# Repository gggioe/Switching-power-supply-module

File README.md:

# Switching-power-supply-module
SIC450 power supply board

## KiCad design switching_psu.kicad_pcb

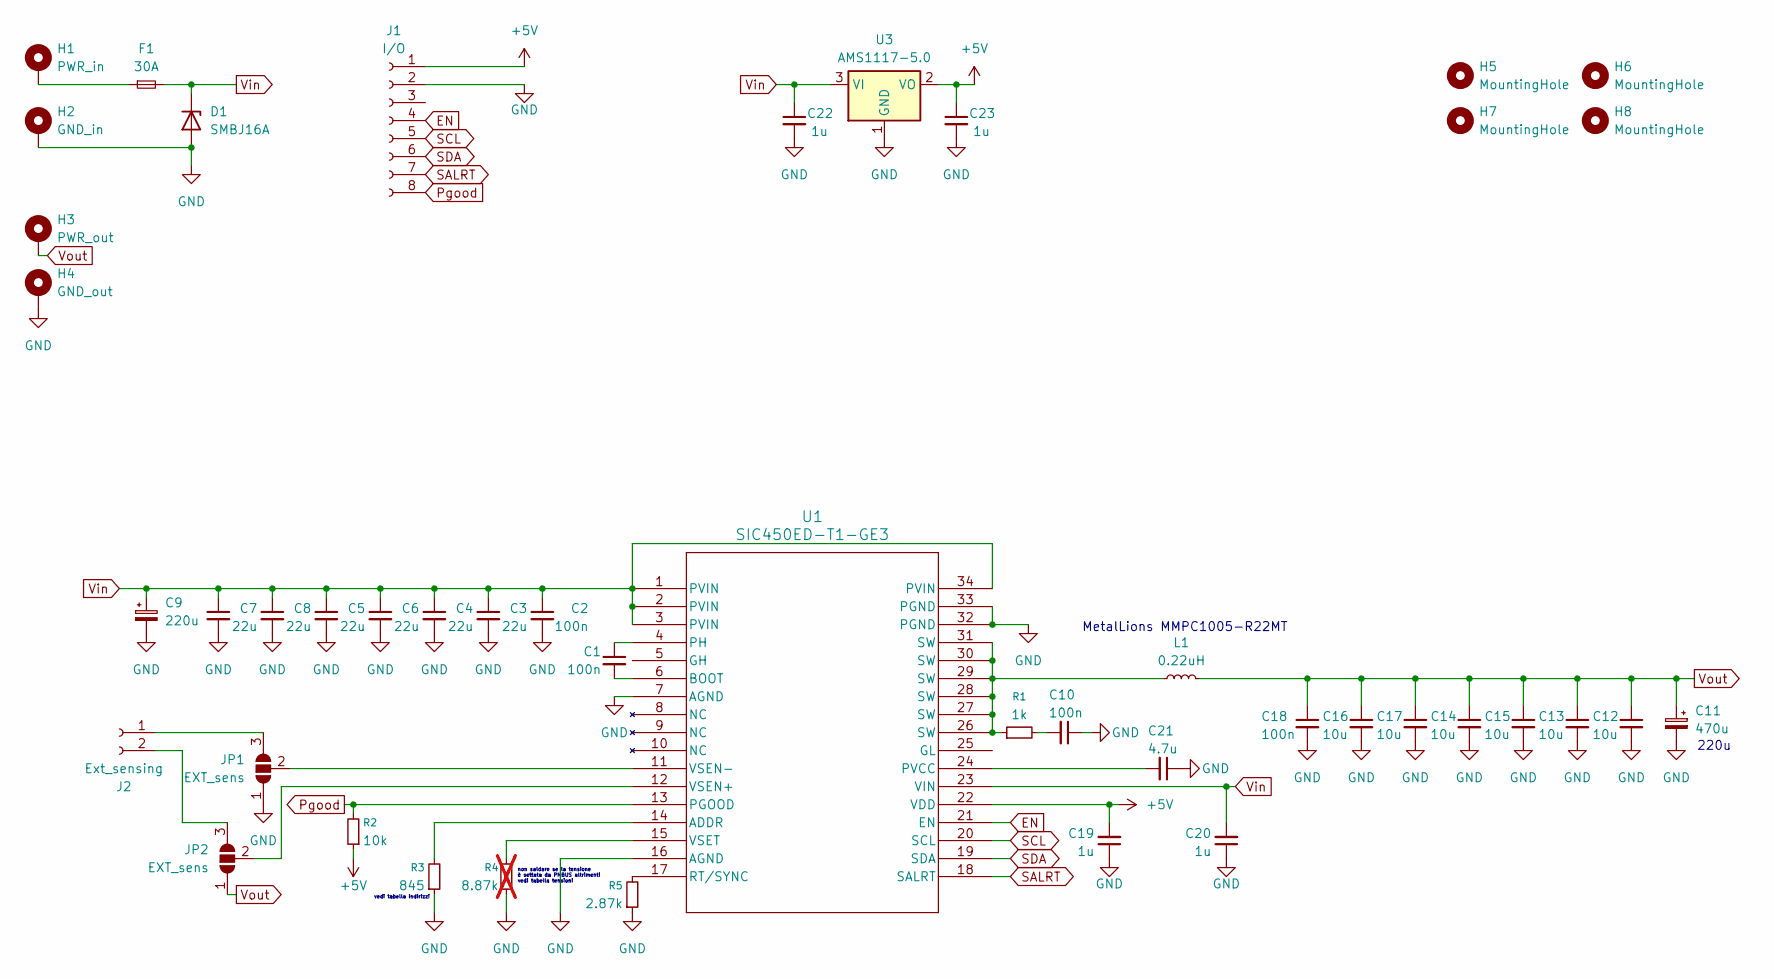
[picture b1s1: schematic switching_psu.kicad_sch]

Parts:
C1, C2, C10, C18: 100n; C_0603_1608Metric_Pad1.08x0.95mm_HandSolder
C3, C4, C5, C6, C7, C8: 22u; C_0805_2012Metric_Pad1.18x1.45mm_HandSolder
C9: 220u; C_Elec_6.3x7.7
C11: 470u; C_Elec_6.3x7.7
C12, C13, C14, C15, C16, C17: 10u; C_0603_1608Metric_Pad1.08x0.95mm_HandSolder
C19, C20, C22, C23: 1u; C_0603_1608Metric_Pad1.08x0.95mm_HandSolder
C21: 4.7u; C_0603_1608Metric_Pad1.08x0.95mm_HandSolder
D1: SMBJ16A; D_SMB_Handsoldering
F1: 30A; Fuse_1206_3216Metric_Pad1.42x1.75mm_HandSolder
H1: PWR_in; MountingHole_4.3mm_M4_Pad_Via
H2: GND_in; MountingHole_4.3mm_M4_Pad_Via
H3: PWR_out; MountingHole_4.3mm_M4_Pad_Via
H4: GND_out; MountingHole_4.3mm_M4_Pad_Via
H5, H6, H7, H8: MountingHole; MountingHole_4.3mm_M4
J1: I/O; JST_PH_B8B-PH-K_1x08_P2.00mm_Vertical
J2: Ext_sensing; JST_PH_B2B-PH-K_1x02_P2.00mm_Vertical
JP1, JP2: EXT_sens; SolderJumper-3_P1.3mm_Open_RoundedPad1.0x1.5mm
L1: 0.22uH; L_12x12mm_H6mm
R1: 1k; R_0603_1608Metric_Pad0.98x0.95mm_HandSolder
R2: 10k; R_0603_1608Metric_Pad0.98x0.95mm_HandSolder
R3: 845; R_0603_1608Metric_Pad0.98x0.95mm_HandSolder
R4: 8.87k; R_0603_1608Metric_Pad0.98x0.95mm_HandSolder; not fitted
R5: 2.87k; R_0603_1608Metric_Pad0.98x0.95mm_HandSolder
U1: SIC450ED-T1-GE3; POWERPAK_MLP34-57_VIS
U3: AMS1117-5.0; SOT-223-3_TabPin2

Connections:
+5V: C19.2, C23.1, J1.1, R2.1, U1.22 (VDD), U3.2 (VO)
EN: J1.4, U1.21 (EN)
GND: C2.2, C3.2, C4.2, C5.2, C6.2, C7.2, C8.2, C9.2, C10.1, C11.2, C12.2, C13.2, C14.2, C15.2, C16.2, C17.2, C18.2, C19.1, C20.1, C21.1, C22.2, C23.2, D1.2 (A), H2.1, H4.1, J1.2, JP1.1 (A), R3.1, R4.1, R5.1, U1.7 (AGND), U1.16 (AGND), U1.32 (PGND), U1.33 (PGND), U3.1 (GND)
unnamed: C10.2, R1.2
unnamed: F1.1, H1.1
unnamed: J2.1, JP1.3 (B)
unnamed: J2.2, JP2.3 (B)
unnamed: JP1.2 (C), U1.11 (VSEN-)
unnamed: JP2.2 (C), U1.12 (VSEN+)
unnamed: L1.1, R1.1, U1.26 (SW), U1.27 (SW), U1.28 (SW), U1.29 (SW), U1.30 (SW), U1.31 (SW)
unnamed: R3.2, U1.14 (ADDR)
unnamed: C1.2, U1.6 (BOOT)
unnamed: C1.1, U1.4 (PH)
unnamed: C21.2, U1.24 (PVCC)
unnamed: R5.2, U1.17 (RT/SYNC)
unnamed: R4.2, U1.15 (VSET)
Pgood: J1.8, R2.2, U1.13 (PGOOD)
SALRT: J1.7, U1.18 (SALRT)
SCL: J1.5, U1.20 (SCL)
SDA: J1.6, U1.19 (SDA)
Vin: C2.1, C3.1, C4.1, C5.1, C6.1, C7.1, C8.1, C9.1, C20.2, C22.1, D1.1 (K), F1.2, U1.1 (PVIN), U1.2 (PVIN), U1.3 (PVIN), U1.23 (VIN), U1.34 (PVIN), U3.3 (VI)
Vout: C11.1, C12.1, C13.1, C14.1, C15.1, C16.1, C17.1, C18.1, H3.1, JP2.1 (A), L1.2

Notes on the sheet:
non saldare se la tensione è settata da PMBUS altrimenti vedi tabella tensioni
vedi tabella indirizzi
220u
MetalLions MMPC1005-R22MT

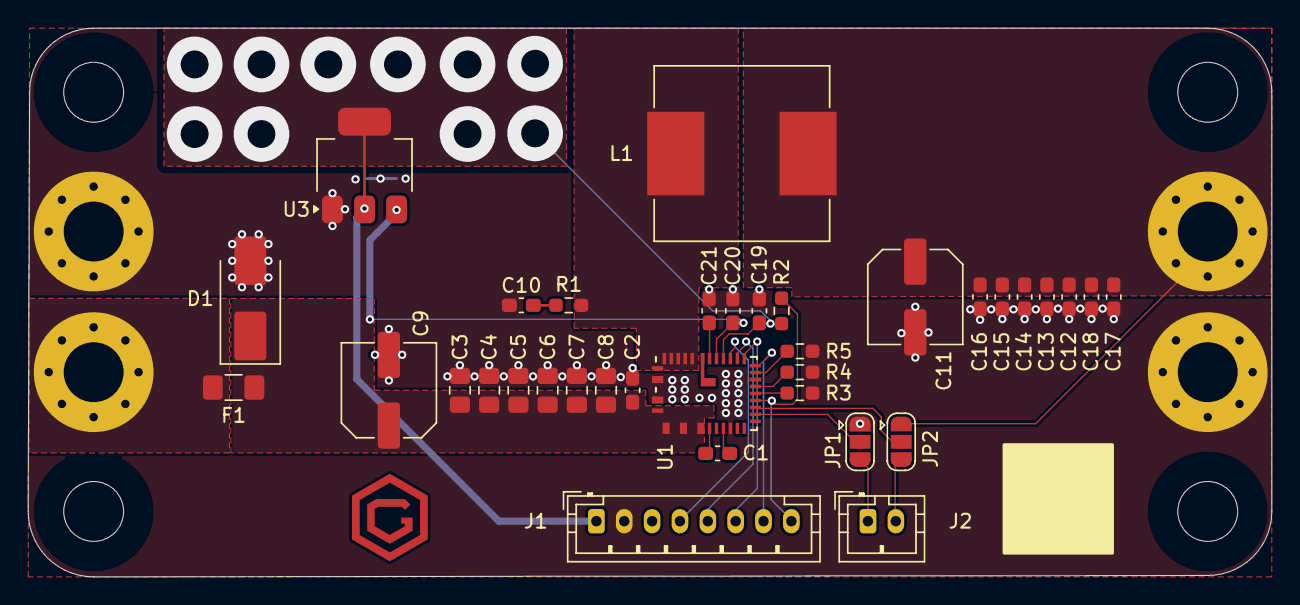
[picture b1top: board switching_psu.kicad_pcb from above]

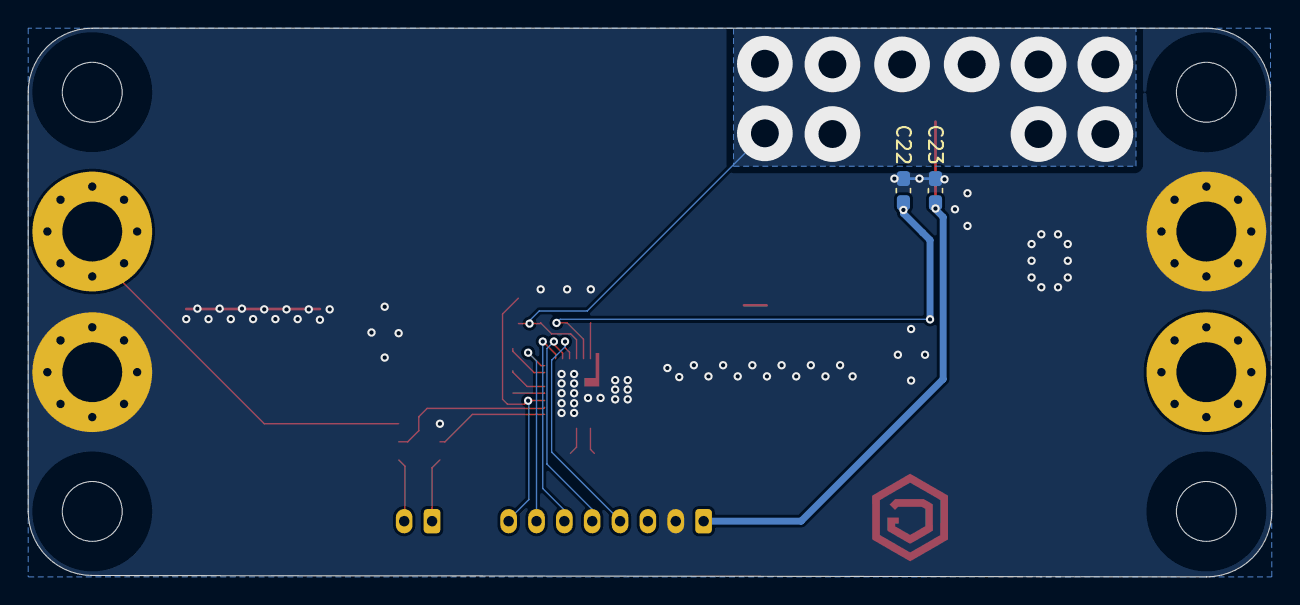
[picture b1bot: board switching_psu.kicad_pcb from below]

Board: 4 copper layers, 89.3 x 39.4 mm, 45 parts (2 on the bottom side), 22 nets.

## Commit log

2025-09-17 Create folder
